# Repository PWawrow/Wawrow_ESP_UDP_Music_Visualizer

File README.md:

| Supported Targets | ESP32 |

Only started Testing

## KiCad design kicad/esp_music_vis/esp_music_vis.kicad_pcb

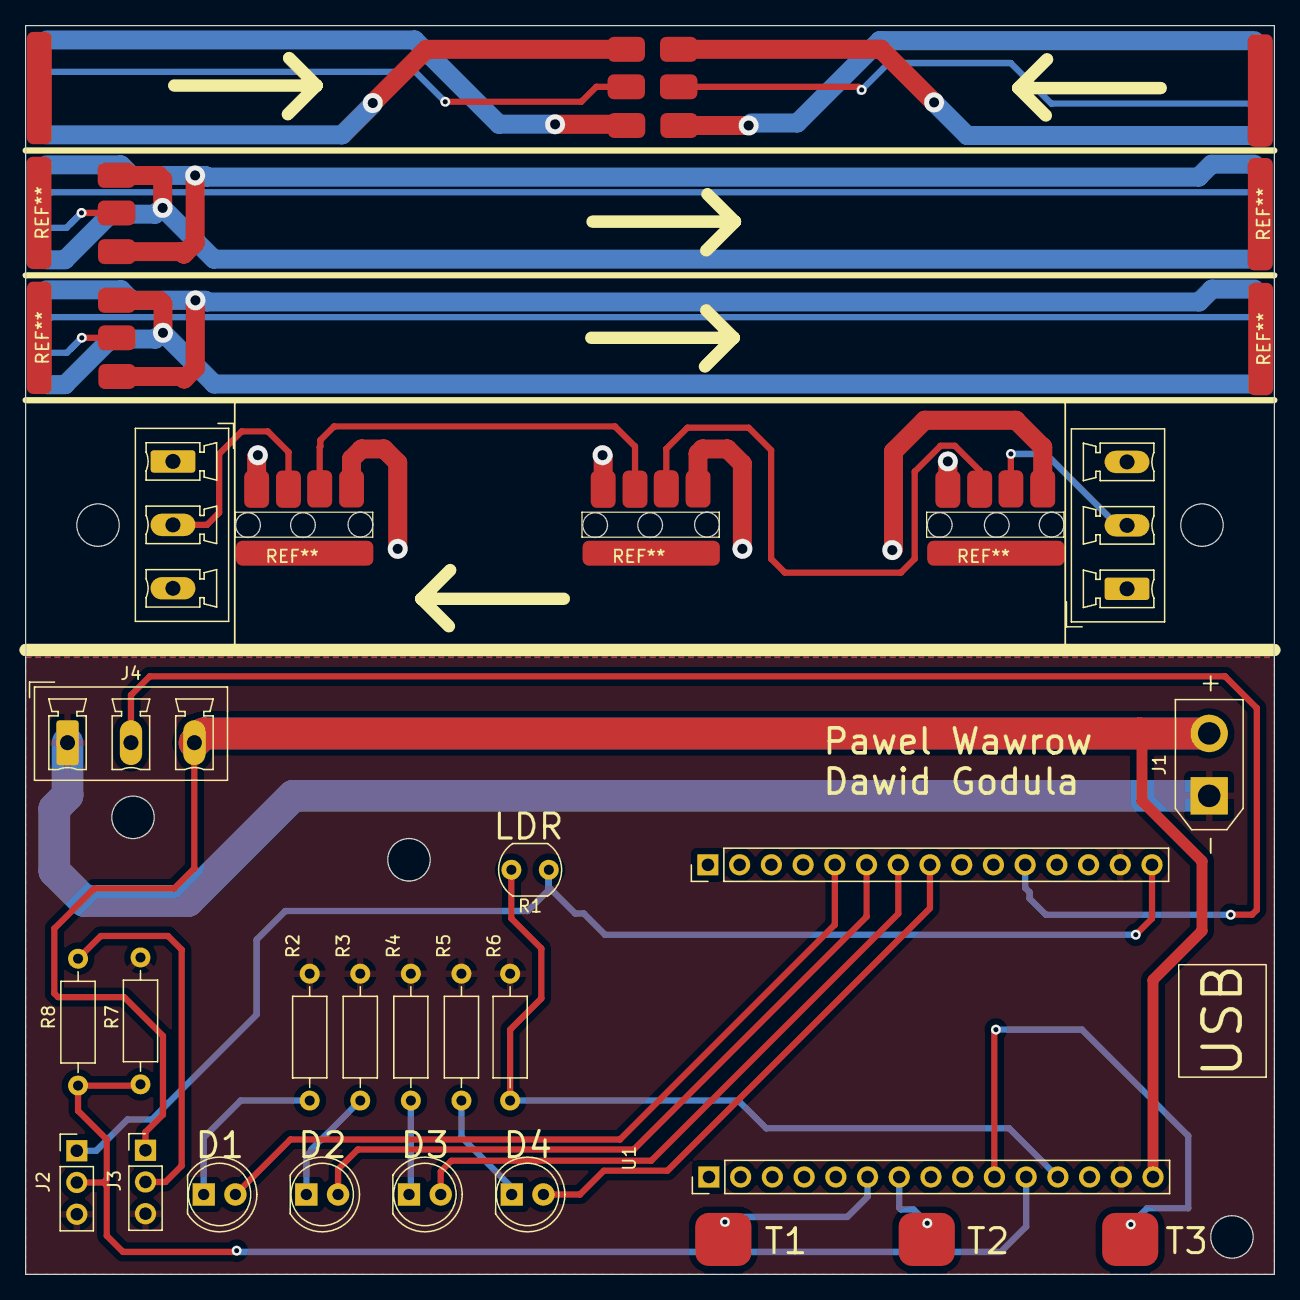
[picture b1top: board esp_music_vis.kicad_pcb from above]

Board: 2 copper layers, 100.0 x 100.0 mm, 19 parts (0 on the bottom side), 15 nets.

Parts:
D1, D2, D3, D4: LED; LED_D5.0mm_Clear
J1: Conn_01x02_Pin; AMASS_XT30UPB-M_1x02_P5.0mm_Vertical
J2, J3: Conn_01x03_Pin; PinHeader_1x03_P2.54mm_Vertical
J4, J4#2, J4#3: Conn_01x03_Pin; PhoenixContact_MCV_1,5_3-G-5.08_1x03_P5.08mm_Vertical
R1: R_Photo; R_LDR_5.0x4.1mm_P3mm_Vertical
R2, R3, R4, R5: 260; R_Axial_DIN0207_L6.3mm_D2.5mm_P10.16mm_Horizontal
R6, R7: 10k; R_Axial_DIN0207_L6.3mm_D2.5mm_P10.16mm_Horizontal
R8: 5.1k; R_Axial_DIN0207_L6.3mm_D2.5mm_P10.16mm_Horizontal
U1: ESP32_WROOM_32D_devkit; ESP32_WROOM_DEV_30PIN

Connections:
+3.3V: J2.1, R1.1, U1.30 (3V3)
+5V: J1.2, J3.1, J4.3, J4#2.3, U1.15 (VIN)
GND: J1.1, J2.3, J3.3, J4.1, J4#2.1, J4#3.3, R2.2, R3.2, R4.2, R5.2, R6.2, R7.1, U1.14 (GND), U1.29 (GND)
LED1: D1.2 (A), U1.20 (D21)
LED2: D2.2 (A), U1.21 (D19)
LED3: D3.2 (A), U1.22 (D18)
LED4: D4.2 (A), U1.23 (D5)
LED_DOUT: J4#2.2, U1.26 (D4)
L_SENSOR: R1.2, R6.1, U1.12 (D12)
MOTION: J2.2, R7.2, R8.1, U1.11 (D14)
unnamed: D1.1 (K), R2.1
unnamed: D2.1 (K), R3.1
unnamed: D3.1 (K), R4.1
unnamed: D4.1 (K), R5.1
unnamed: J3.2, R8.2

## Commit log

2024-10-08 First Commit, Kind of working!
2024-10-08 After Some Clearing
2024-10-08 Change README
2024-10-08 Added welcome effect and rgbw_write(pixels)func
2024-10-09 Added PCB design!
2024-10-16 PCB first version
2024-11-01 working-good music visualization, changing settings of vis to be added
2024-11-01 mdns working!
2024-11-01 add Menu Task + clear LEDS on udpserver error
2024-11-02 Added Menu Task + Updated UDPServer to perform suspend
